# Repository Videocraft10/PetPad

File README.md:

# PetPad [WIP]

Custom-Made Tamagotchi-Like Device

## Features

### Physical
1. USB - C rechargeable 500 mAh battery
2. 3 Tactile buttons for control
3. Buzzer for sound feedback
4. 128x64 OLED Screen

### Digital
1. [WIP] Multiple Pets to obtain
2. Take care (or don't) of your pets to see the visuals change
3. [WIP] Use items obtained randomly on your pets for effects

## Why?
I wanted to create this for a couple of reasons:
1. I wanted a more complex project to work on
2. Tamagotchis are fun and allow me to practice some pixel art skills too
3. And finally, because there was a great guide on the Fallout docs :)

## The PCB
The PCB was made in KiCAD due to the extensive tools and ability to import own footprints that might not be on EasyEDA

### The Schematic

### The Circuit Board
**Front**

**Back**

## The Case

**Overview**

**Top**

**Inside cut**

**Bottom**

## The Firmware

Visible stats that change over time with visual feedback on overall pets health

## BOM
*Amount used is to make ****ONE**** PetPad*

| Item | LCSC # / Item Links | Single Cost | Amount Used | Fees/Notes | Total Price |
| ---------- | ---------- | ---------- | ---------- | ---------- | ---------- |
| **PCB:** | ---------- | $2 | 1 | $3.12 for shipping | $5.12 |
| ---------- | ---------- | ---------- | ---------- | ---------- | ---------- |
| **Components:** | ---------- | ---------- | ---------- | ---------- | ---------- |
| OLED Screen | [C5248080](https://www.lcsc.com/product-detail/C5248080.html?spm=wm.gwc.xh.0.cbm___wm.mly.ssl.gwc&lcsc_vid=QwcNU1RVElVcAVECegBfXwdeFFZXVlUDQlMMBlFRRFQxVlNRQVZfV1NeRFVYVzsOAxUeFF5JWBYZEEoKFBINSQcJGk4NBhYS) | $2.32 | 1 | ---------- | $2.32 |
| Buzzer | [C49246964](https://www.lcsc.com/product-detail/C49246964.html?spm=wm.gwc.xh.1.cbm___wm.mly.ssl.gwc&lcsc_vid=QwcNU1RVElVcAVECegBfXwdeFFZXVlUDQlMMBlFRRFQxVlNRQVZfV1NeRFVYVzsOAxUeFF5JWBYZEEoKFBINSQcJGk4NBhYS) | $0.0569 | 1 | Forced to buy 10 | $0.57 |
| Buttons | [C2888493](https://www.lcsc.com/product-detail/C2888493.html?spm=wm.gwc.xh.2.cbm___wm.mly.ssl.gwc&lcsc_vid=QwcNU1RVElVcAVECegBfXwdeFFZXVlUDQlMMBlFRRFQxVlNRQVZfV1NeRFVYVzsOAxUeFF5JWBYZEEoKFBINSQcJGk4NBhYS) | $0.0107 | 3 | Forced to buy 50 | $0.54 |
| JST Battery Connector | [C131337](https://www.lcsc.com/product-detail/C131337.html?spm=wm.gwc.xh.3.cbm___wm.mly.ssl.gwc&lcsc_vid=QwcNU1RVElVcAVECegBfXwdeFFZXVlUDQlMMBlFRRFQxVlNRQVZfV1NeRFVYVzsOAxUeFF5JWBYZEEoKFBINSQcJGk4NBhYS) | $0.0336 | 1 | Forced to buy 20 | $0.67 |
| 7 Pin Header | [C5360900](https://www.lcsc.com/product-detail/C5360900.html?spm=wm.gwc.dh.4.cbm___wm.mly.ssl.gwc&lcsc_vid=QwcNU1RVElVcAVECegBfXwdeFFZXVlUDQlMMBlFRRFQxVlNRQVZfV1NeRFVYVzsOAxUeFF5JWBYZEEoKFBINSQcJGk4NBhYS) | $0.0391 | 2 | Forced to buy 10 | $0.39 |
| 4 Pin Header | [C42431787](https://www.lcsc.com/product-detail/C42431787.html?s_z=n_q_PZ2.54-1*4&spm=wm.fly.bg.10.xh&lcsc_vid=TgBXAwYAFVlYUAdXQVhcUVUFQABXXlJeElANBlxRQAIxVlNRTlFbUVRRQ1VcVDsOAxUeFF5JWBYZEEoKFBINSQcJGk4dAgUUFBIk%3D) | $0.0207 | 1 | Forced to buy 20 | $0.41 |
| Seeed Studio XIAO C6 DIP | [Amazon](https://www.amazon.com/ESP32C6-Supports-Bluetooth-802-15-4-Microsoft/dp/B0D2NKV334?th=1) | $11.99 | 1 | $0.79 tax | $12.78 |
| Battery (140mAh) | [AliExpress](https://www.aliexpress.us/item/3256808031709894.html?channel=twinner) | $1.06 | 1 | NOTE: INSANE SUMMER DEAL USED, NORMAL PRICE $14.23 | $1.06 |
| Screws (M2.5 x 5mm) | [Homedepot](https://www.homedepot.com/p/Prime-Line-M2-5-0-45-x-5-mm-Grade-A2-70-Stainless-Steel-Phillips-Drive-Pan-Head-Metric-Machine-Screws-10-Pack-9130825/311229791?MERCH=REC-_-rv_search_plp_rr-_-n/a-_-0-_-n/a-_-n/a-_-n/a-_-n/a-_-n/a-_-n/a) | $0.433 | 4* | 10 pack | $4.33 |
| Wires | [Amazon]([https://www.adafruit.com/product/3169](https://www.amazon.com/Fielect-Enamelled-Winding-Polyurethane-QA-1-155/dp/B082SGDHTT?crid=3POIXT4TOZV8X&dib=eyJ2IjoiMSJ9.w1oH9WPINFywtT7OZmtCDgLDk6IalWVSzi-2-7GuMHuAPawm0k5yT119lFJsF-rJH-uHs1I6qLnd9nLMCaqdH9MYihqoa674noTX4nhzVrpOPF2dk22GB7aIry3RNpuRB0zNbsu97DY79lzWdZ6XJ33oz2e59S97eLn6YiI83coYrCRFQhUi4AvRZS7napdcofGfUDidzUne8SnBlVEOhJjXlK1cI0EN0Mv34Ps6HmY.9FjyuD3y8xoHDIwdMniIMM2knZN64d8aVcBDNQr6chU&dib_tag=se&keywords=30%2Bawg%2Benameled%2Bmagnet%2Bwire&qid=1780683570&sprefix=30%2Bawg%2B%2Caps%2C362&sr=8-4)) | $7.48 | less than a foot most likely (WILL HAVE A TON LEFT OVER SO IF YOU HAVE SOMTHING SIMILAR DO NOT BUY) | 30 AWG Magnet Wire Enameled Copper Wire | $7.45 |
| ---------- | ---------- | ---------- | ---------- | ---------- | ---------- |
| *Total:* | ---------- | ---------- | ---------- | ---------- | $37.98 |
| **Fees:** | LCSC Tax $1.25 | ---------- | ---------- | ---------- | [wip] |
| Shipping | LCSC Shipping cost: $10.92 | ---------- | ---------- | ---------- | [wip]|
| Handling | LCSC Handling $3 | ---------- | ---------- | ---------- | $3 |
| ---------- | ---------- | ---------- | ---------- | ---------- | ---------- |
| ***TOTAL*** | ---------- | ---------- | ---------- | ---------- | $50.30 (fee prices not locked in yet) |

## Build BOM
| Item | Discripton | Notes | Fees | -------- | Total |
| ---------- | ---------- | ---------- | ---------- | ---------- | ---------- |
| 3D Printer PLA | Generic 3D printer PLA. Requires a 3D printer to use | Paid $8.34 for 1 kg | ---------- | ---------- | 46g used - $0.38 |
| Sodering Iron | ---------- | Required to soder on components | ---------- | ---------- | $10.55 [here](https://www.amazon.com/Soldering-Digital-Welding-Portable-Electric/dp/B08R3515SF?crid=30SL6CYRR5QOM&dib=eyJ2IjoiMSJ9.tKWBCBm44gyjNSvFj51RHR3p5aTdCOPIkPv4zqdgg07Moy7biWvfE6YjBdwHnsMMUqJ5p1WsD_MQe5r0XLalW_yVXgv5tx_TBmzJ2sAt1If-sll8ak-_muURnXvGQ8DVMdb2n-LQRQO0gSH2GR3nmbYitK2dPQ3w6Pu08Y6wdY2s8pWVOnGJz7T9gRpbqCr_TALWvgprG9lNvJy1RXWeywEfL33os00Syai0ic4byZ-FLX-ZYRh2TATM8PfFfGRYe0N_YCACfh6VRKp0zii5u79dBTlHN-xO9SU5h5X_axQ.4EqxHoftylAQD1t5h9kA999EhPS51LAq9y_vrFTic5Y&dib_tag=se&keywords=soldering%2Biron&qid=1780680980&sprefix=sodering%2Bir%2Caps%2C290&sr=8-6&th=1) |
| ---------- | ---------- | ---------- | ---------- | ---------- | ---------- |
| ***TOTAL*** | ---------- | ---------- | ---------- | ---------- | $10.93 |

***GRAND TOTAL*** = $60.68

## How to Build
> [!NOTE]
> It is recommended to have prior knowledge in electronics and soldering if you want to create one for yourself!

First download the PCB Gerber file from [here](https://github.com/Videocraft10/PetPad/tree/main/PCB%20Files) then send it to your preferred manufacturer! Next buy all of the components from the BOM. For screws and similar items, it is recommended to find the cheapest in your location. Next 3D print the case from here [here](https://github.com/Videocraft10/PetPad/tree/main/Case%20Files) and ensure the PCB fits once it arrives. Next solder on all of the components and screw the PCB into the case! Finally flash the firmware onto it from [here](https://github.com/Videocraft10/PetPad/tree/main/Firmware%20Files/PetPad_Firm) (you might have to build the file on you own computer)

Tada! You now have a PetPad!

(instructions on how to build will improves once I actually physically build one myself :D)

## Software Used
1. KiCAD
2. Autodesk Fusion
3. Blender
4. Visual Studio Code (Arduino Maker Workshop & Wokwi extentsihons)
5. Arduino IDE
6. Adobe Photoshop
7. Adobe Preimimre Pro
8. Visual Studio Code

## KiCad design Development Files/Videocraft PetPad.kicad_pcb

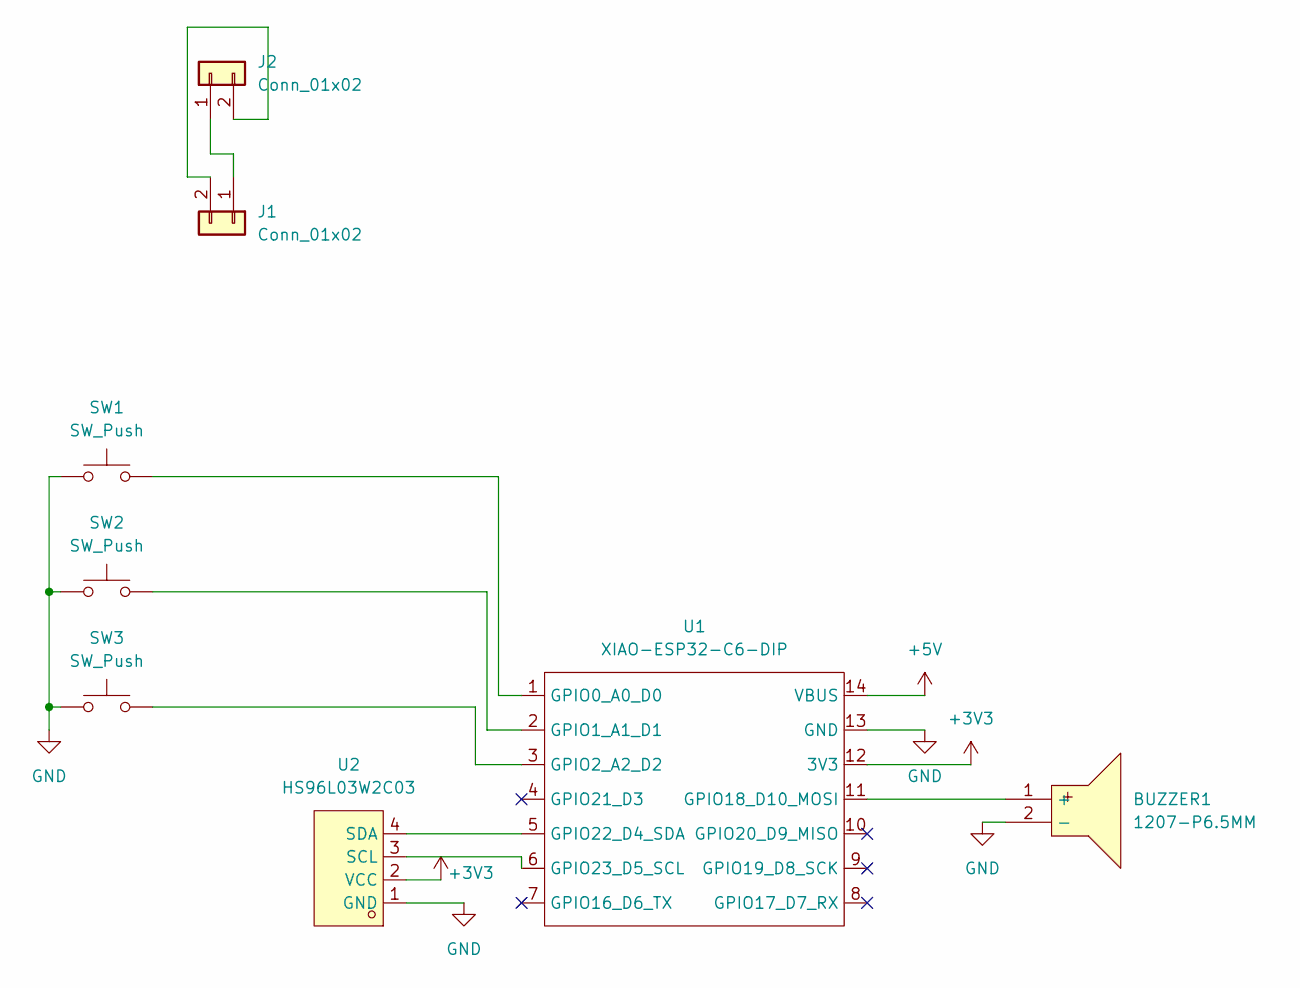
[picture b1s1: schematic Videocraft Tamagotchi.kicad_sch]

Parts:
BUZZER1: 1207-P6.5MM; BUZ-TH_BD12.5-P6.50-D1.4; MPN 1207-P6.5MM; LCSC Part C49246964
J1: Conn_01x02; SolderWire-0.5sqmm_1x02_P4.6mm_D0.9mm_OD2.1mm
J2: Conn_01x02; JST_PH_B2B-PH-K_1x02_P2.00mm_Vertical
SW1, SW2, SW3: SW_Push; SW-TH_4P-L4.5-W4.5-P3.00-LS4.8
U1: XIAO-ESP32-C6-DIP
U2: HS96L03W2C03; OLED-TH_L27.8-W27.2-P2.54_C9900033791; MPN HS96L03W2C03; LCSC Part C5248080

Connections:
+3V3: U1.12 (3V3), U2.2 (VCC)
+5V: U1.14 (VBUS)
GND: BUZZER1.2 (-), SW1.1, SW2.1, SW3.1, U1.13 (GND), U2.1 (GND)
unnamed: BUZZER1.1 (+), U1.11 (GPIO18_D10_MOSI)
unnamed: J1.1, J2.1
unnamed: J1.2, J2.2
unnamed: SW1.2, U1.1 (GPIO0_A0_D0)
unnamed: SW2.2, U1.2 (GPIO1_A1_D1)
unnamed: SW3.2, U1.3 (GPIO2_A2_D2)
unnamed: U1.5 (GPIO22_D4_SDA), U2.4 (SDA)
unnamed: U1.6 (GPIO23_D5_SCL), U2.3 (SCL)

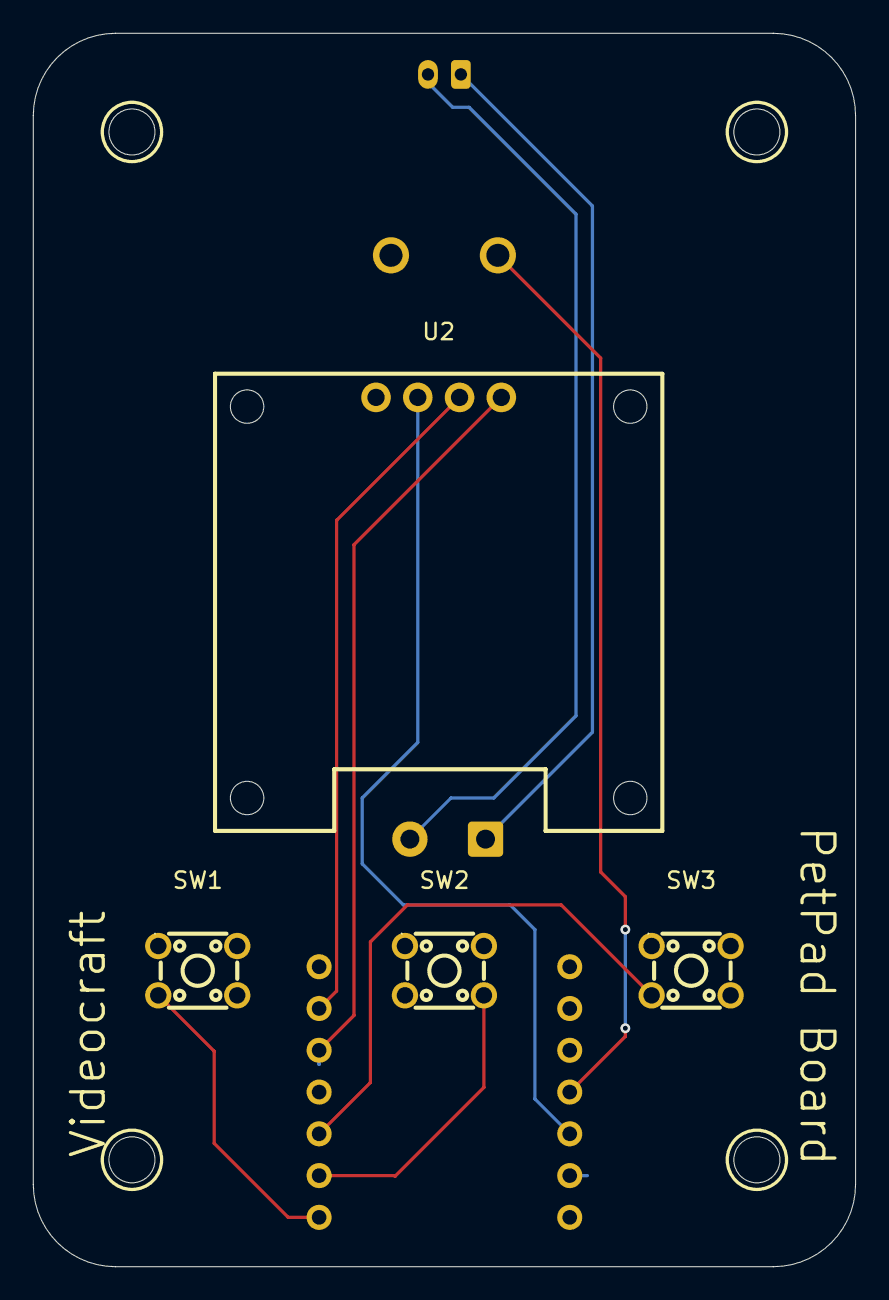
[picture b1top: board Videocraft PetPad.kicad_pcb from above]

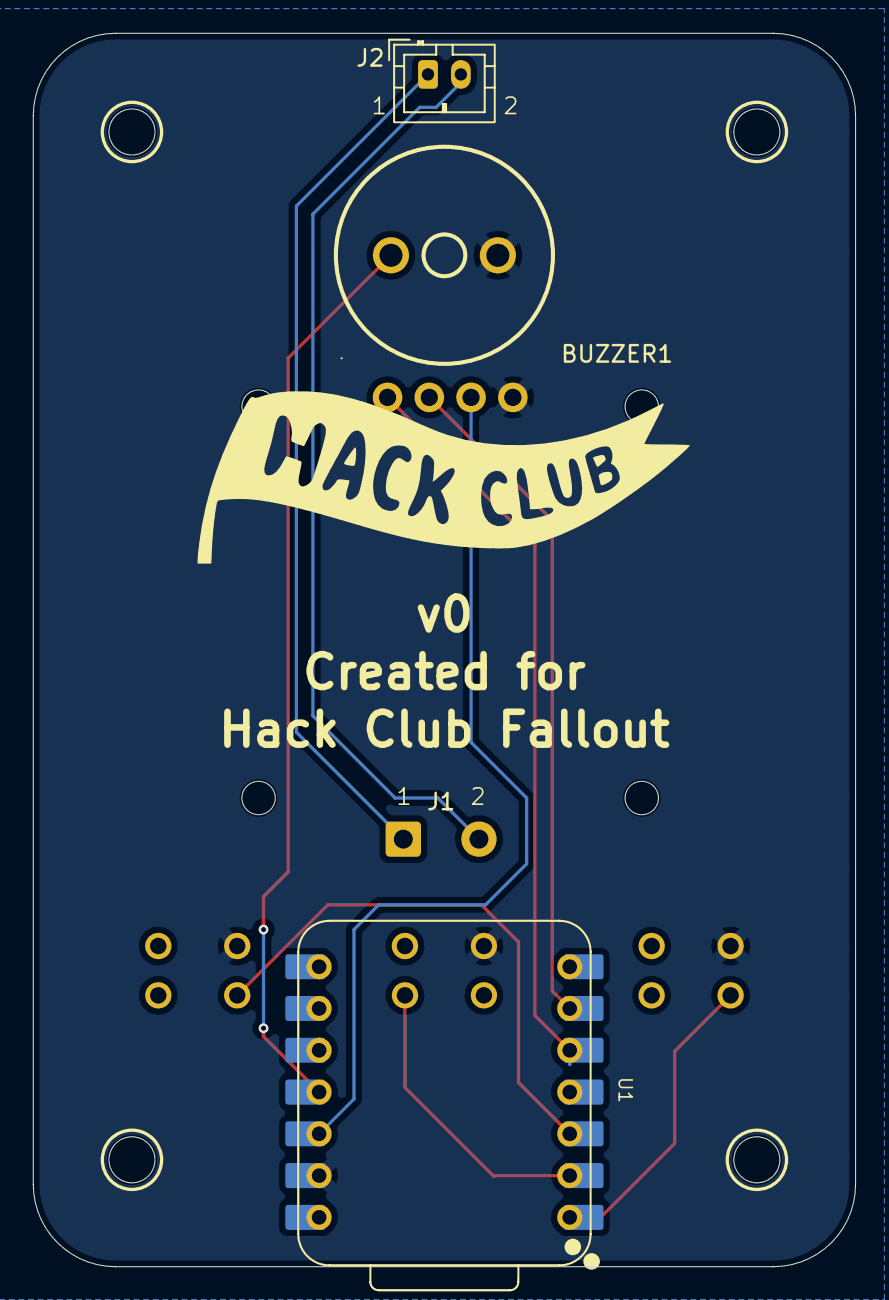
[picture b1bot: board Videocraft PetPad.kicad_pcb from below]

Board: 2 copper layers, 50.0 x 75.0 mm, 8 parts (4 on the bottom side), 10 nets.

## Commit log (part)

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2026-05-16 Update README with BOM and cost details
    Added detailed cost breakdown for components and fees.
2026-05-16 Setup Files
    Added some organization folders, added KiCad production files, added PCB 3D models, added PCB Gerber files.
2026-05-16 Removed unnecessary folder
    And updated file names
2026-05-17 Added Componet Step Files
2026-05-19 Updated .step files for headers
2026-05-22 Update screw specifications in README
2026-05-23 Exported CAD Files and 3D Print Files
    Plus added a simple repo cover image
2026-05-23 Add cover image to README
    Added an image to the README for visual representation.
2026-05-23 Firmware files added
    Also reorganized some folders
2026-05-26 Firmware Arduino setup and first Sprite pic
    Setup the visual studio code addon for Arduino projects, made buttons do stuff and buzzer ring, also made first pet sprite.
2026-05-27 Created more sprites and implemented them in code
2026-05-27 Enhance README with features and project details
    Added detailed features, PCB information, case overview, BOM, and software used sections to README.
2026-05-30 Added debug logs and new build
2026-05-30 Update Stat screen and fix wokwi sim
2026-05-31 Update README with firmware section and video
    Added a section about the firmware and included a video.
2026-06-01 Promo Gif and github cover pic v2
2026-06-01 Add main image to README and update cover image
2026-06-01 Updated CAD files and zine progress
2026-06-02 Added lights to zine, background, and a qr code
2026-06-04 update zine
2026-06-04 THE FINAL ZINE
2026-06-04 Update total costs and grand total in README
    Updated total costs and grand total in the README.
2026-06-04 Fix spelling mistakes in README.md (preserve all information and links)
2026-06-05 Update total fees and add BOM section in README
2026-06-05 Update battery price and fees in BOM
2026-06-05 Update soldering iron price and total cost
2026-06-10 KiCad Removed due to switching to easyeda
2026-06-10 Revert "KiCad Removed due to switching to easyeda"
    This reverts commit 66cc2478bb831fb9d475607df87d2e1e71403cc5.
2026-06-12 Update BOM
2026-06-12 Fix spelling errors in README instructions
    Corrected spelling errors in the instructions for building the PetPad.
